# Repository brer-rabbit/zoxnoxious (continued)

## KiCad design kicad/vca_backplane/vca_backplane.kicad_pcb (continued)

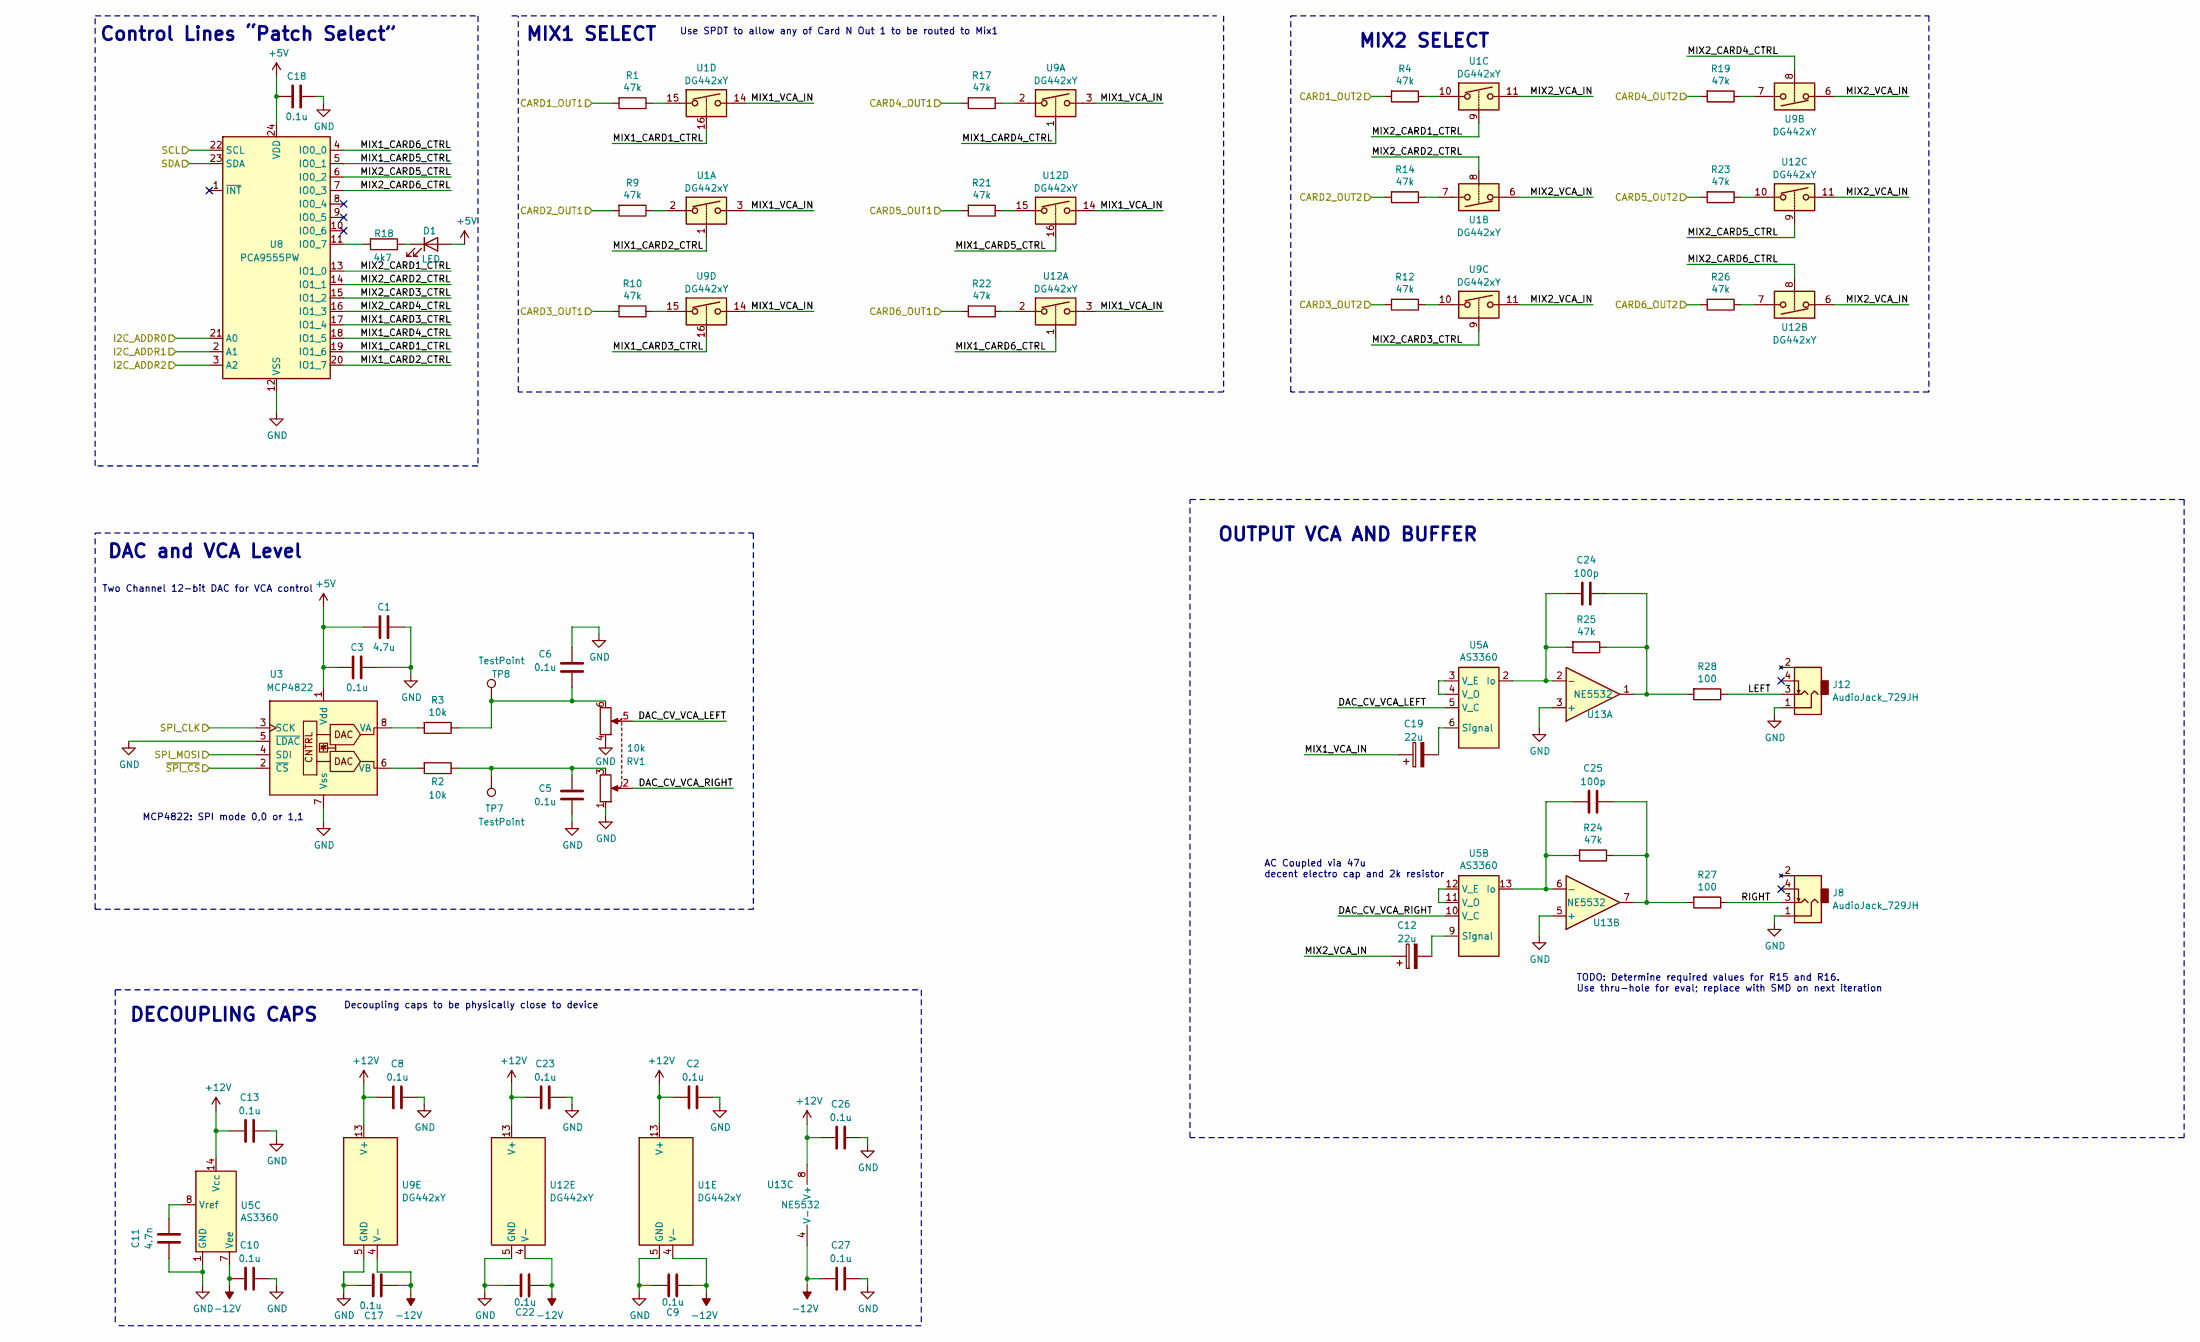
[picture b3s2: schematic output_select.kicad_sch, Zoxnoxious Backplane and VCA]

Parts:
C1: 4.7u; C_0805_2012Metric; LCSC C1779
C2, C3, C5, C6, C8, C9, C10, C13, C17, C18, C22, C23, C26, C27: 0.1u; C_0603_1608Metric; LCSC C14663
C11: 4.7n; C_0603_1608Metric; LCSC C53987
C12, C19: 22u; CP_Radial_D6.3mm_P2.50mm; Digikey 493-10780-1-ND
C24, C25: 100p; C_0603_1608Metric; LCSC C14858
D1: LED; LED_0603_1608Metric; LCSC C2286
J8, J12: AudioJack_729JH; Jack_3.5mm_729JH-R_Horizontal
R1, R4, R9, R10, R12, R14, R17, R19, R21, R22, R23, R24, R25, R26: 47k; R_0603_1608Metric; LCSC C25819
R2, R3: 10k; R_0603_1608Metric; LCSC C25804
R18: 4k7; R_0603_1608Metric; LCSC C23162
R27, R28: 100; R_0603_1608Metric; LCSC C22775
RV1: 10k; TRIM_PTN092-H10115K1B; Digikey PTN092-H10115K1A
TP7, TP8: TestPoint; TestPoint_Pad_2.0x2.0mm; Digikey 952-2664-2-ND
U1, U9, U12: DG442xY; SOIC-16_3.9x9.9mm_P1.27mm; LCSC C2673321
U3: MCP4822; SOIC-8_3.9x4.9mm_P1.27mm; LCSC C16040
U5: AS3360; SOIC-14_3.9x8.7mm_P1.27mm
U8: PCA9555PW; TSSOP-24_4.4x7.8mm_P0.65mm; LCSC C83265
U13: NE5532; SOIC-8_3.9x4.9mm_P1.27mm; LCSC C7426

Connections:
+5V: C1.2, C3.2, C18.2, D1.2 (A), U3.1 (Vdd), U8.2 (A1), U8.3 (A2), U8.21 (A0), U8.24 (VDD); also elsewhere on the board
+12V: C2.1, C8.1, C13.1, C23.1, C26.1, U1.13 (V+), U5.14 (Vcc), U9.13 (V+), U12.13 (V+), U13.8 (V+); also elsewhere on the board
-12V: C9.2, C10.1, C17.2, C22.2, C27.1, U1.4 (V-), U5.7 (Vee), U9.4 (V-), U12.4 (V-), U13.4 (V-); also elsewhere on the board
/CARD1_OUT1: R1.2; also elsewhere on the board
/CARD1_OUT2: R4.2; also elsewhere on the board
/CARD2_OUT1: R9.2; also elsewhere on the board
/CARD2_OUT2: R14.2; also elsewhere on the board
/CARD3_OUT1: R10.2; also elsewhere on the board
/CARD3_OUT2: R12.2; also elsewhere on the board
/CARD4_OUT1: R17.2; also elsewhere on the board
/CARD4_OUT2: R19.2; also elsewhere on the board
/CARD5_OUT1: R21.2; also elsewhere on the board
/CARD5_OUT2: R23.2; also elsewhere on the board
/CARD6_OUT1: R22.2; also elsewhere on the board
/CARD6_OUT2: R26.2; also elsewhere on the board
/SCL_5V: U8.22 (SCL); also elsewhere on the board
/SDA_5V: U8.23 (SDA); also elsewhere on the board
/SPI_CLK2_5V: U3.3 (SCK); also elsewhere on the board
/SPI_CS0_H: U3.2 (~CS); also elsewhere on the board
/SPI_MOSI2_5V: U3.4 (SDI); also elsewhere on the board
/Sheet624DD88D/DAC_CV_VCA_LEFT: RV1.5, U5.5 (V_C)
/Sheet624DD88D/DAC_CV_VCA_RIGHT: RV1.2, U5.10 (V_C)
/Sheet624DD88D/LEFT: J12.3, R28.1
/Sheet624DD88D/MIX1_CARD1_CTRL: U1.16, U8.19 (IO1_6)
/Sheet624DD88D/MIX1_CARD2_CTRL: U1.1, U8.20 (IO1_7)
/Sheet624DD88D/MIX1_CARD3_CTRL: U8.17 (IO1_4), U9.16
/Sheet624DD88D/MIX1_CARD4_CTRL: U8.18 (IO1_5), U9.1
/Sheet624DD88D/MIX1_CARD5_CTRL: U8.5 (IO0_1), U12.16
/Sheet624DD88D/MIX1_CARD6_CTRL: U8.4 (IO0_0), U12.1
/Sheet624DD88D/MIX1_VCA_IN: C19.1, U1.3, U1.14, U9.3, U9.14, U12.3, U12.14
/Sheet624DD88D/MIX2_CARD1_CTRL: U1.9, U8.13 (IO1_0)
/Sheet624DD88D/MIX2_CARD2_CTRL: U1.8, U8.14 (IO1_1)
/Sheet624DD88D/MIX2_CARD3_CTRL: U8.15 (IO1_2), U9.9
/Sheet624DD88D/MIX2_CARD4_CTRL: U8.16 (IO1_3), U9.8
/Sheet624DD88D/MIX2_CARD5_CTRL: U8.6 (IO0_2), U12.9
/Sheet624DD88D/MIX2_CARD6_CTRL: U8.7 (IO0_3), U12.8
/Sheet624DD88D/MIX2_VCA_IN: C12.1, U1.6, U1.11, U9.6, U9.11, U12.6, U12.11
/Sheet624DD88D/RIGHT: J8.3, R27.1
GND: C1.1, C2.2, C3.1, C5.1, C6.2, C8.2, C9.1, C10.2, C11.1, C13.2, C17.1, C18.1, C22.1, C23.2, C26.2, C27.2, J8.1, J12.1, RV1.1, RV1.4, U1.5 (GND), U3.5 (~LDAC), U3.7 (Vss), U5.1 (GND), U8.12 (VSS), U9.5 (GND), U12.5 (GND), U13.3 (+), U13.5 (+); also elsewhere on the board
unnamed: C5.2, R2.1, RV1.3, TP7.1
unnamed: C6.1, R3.1, RV1.6, TP8.1
unnamed: C24.2, R25.1, R28.2, U13.1
unnamed: C25.2, R24.1, R27.2, U13.7
unnamed: D1.1 (K), R18.1
unnamed: R1.1, U1.15
unnamed: R4.1, U1.10
unnamed: R9.1, U1.2
unnamed: R10.1, U9.15
unnamed: R12.1, U9.10
unnamed: R14.1, U1.7
unnamed: R17.1, U9.2
unnamed: R19.1, U9.7
unnamed: R21.1, U12.15
unnamed: R22.1, U12.2
unnamed: R23.1, U12.10
unnamed: R26.1, U12.7
unnamed: R3.2, U3.8 (VA)
unnamed: R2.2, U3.6 (VB)
unnamed: C19.2, U5.6 (Signal)
unnamed: U5.3 (V_E), U5.4 (V_O)
unnamed: C12.2, U5.9 (Signal)
unnamed: U5.11 (V_O), U5.12 (V_E)
unnamed: C11.2, U5.8 (Vref)
unnamed: R18.2, U8.11 (IO0_7)
unnamed: C24.1, R25.2, U5.2 (Io), U13.2 (-)
unnamed: C25.1, R24.2, U5.13 (Io), U13.6 (-)

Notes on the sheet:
Two Channel 12-bit DAC for VCA control
DECOUPLING CAPS
TODO: Determine required values for R15 and R16. Use thru-hole for eval; replace with SMD on next iteration
Decoupling caps to be physically close to device
DAC and VCA Level
Use SPDT to allow any of Card N Out 1 to be routed to Mix1
MIX2 SELECT
OUTPUT VCA AND BUFFER
AC Coupled via 47u decent electro cap and 2k resistor
MCP4822: SPI mode 0,0 or 1,1
MIX1 SELECT
Control Lines “Patch Select”

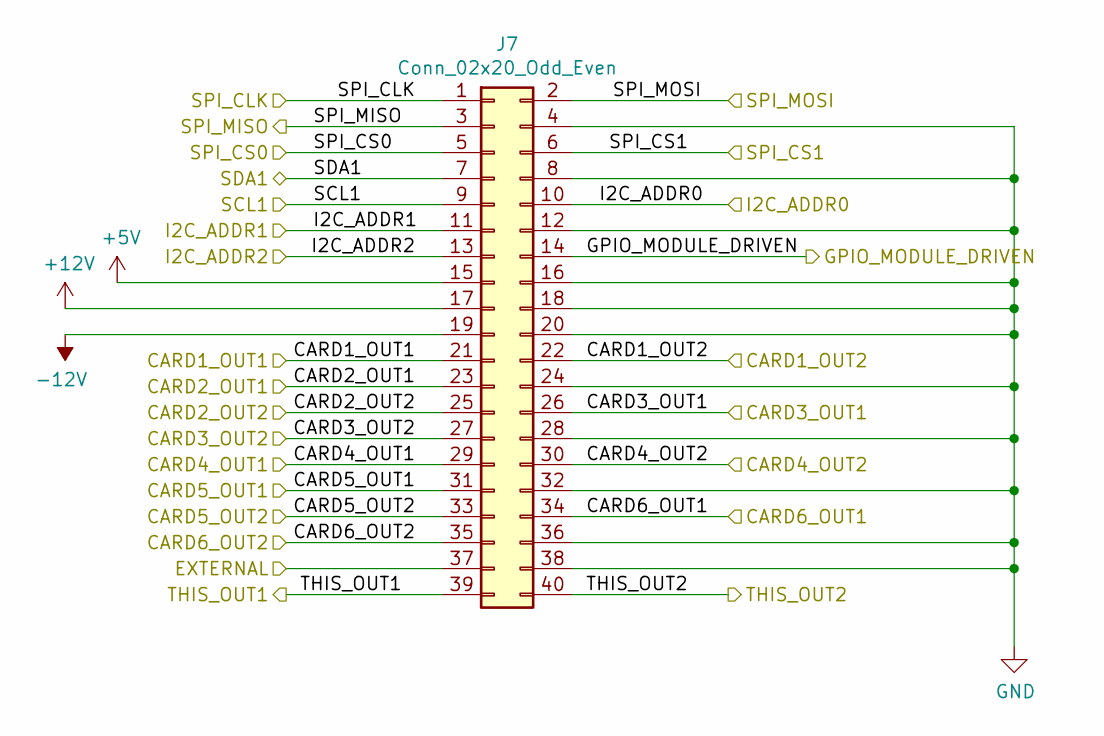
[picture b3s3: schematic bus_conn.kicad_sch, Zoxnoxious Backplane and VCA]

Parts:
J7: Conn_02x20_Odd_Even; PinSocket_2x20_P2.54mm_SullinsPolarized; Digikey S9200-ND

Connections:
+5V: J7.10, J7.11, J7.15; also elsewhere on the board
+12V: J7.17; also elsewhere on the board
-12V: J7.19; also elsewhere on the board
/CARD1_OUT1: J7.21; also elsewhere on the board
/CARD1_OUT2: J7.22; also elsewhere on the board
/CARD2_OUT1: J7.23; also elsewhere on the board
/CARD2_OUT2: J7.25; also elsewhere on the board
/CARD3_OUT1: J7.26; also elsewhere on the board
/CARD3_OUT2: J7.27; also elsewhere on the board
/CARD4_OUT1: J7.29, J7.39; also elsewhere on the board
/CARD4_OUT2: J7.30, J7.40; also elsewhere on the board
/CARD5_OUT1: J7.31; also elsewhere on the board
/CARD5_OUT2: J7.33; also elsewhere on the board
/CARD6_OUT1: J7.34; also elsewhere on the board
/CARD6_OUT2: J7.35; also elsewhere on the board
/EXTERNAL_AUDIO: J7.37; also elsewhere on the board
/MODULE_D_5V: J7.14; also elsewhere on the board
/SCL_5V: J7.9; also elsewhere on the board
/SDA_5V: J7.7; also elsewhere on the board
/SPI_CLK1_5V: J7.1; also elsewhere on the board
/SPI_CS0_D: J7.5; also elsewhere on the board
/SPI_CS1_D: J7.6; also elsewhere on the board
/SPI_MISO_5V: J7.3; also elsewhere on the board
/SPI_MOSI1_5V: J7.2; also elsewhere on the board
GND: J7.4, J7.8, J7.12, J7.13, J7.16, J7.18, J7.20, J7.24, J7.28, J7.32, J7.36, J7.38; also elsewhere on the board

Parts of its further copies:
J2, J3, J5, J10, J11: Conn_02x20_Odd_Even; PinSocket_2x20_P2.54mm_SullinsPolarized; Digikey S9200-ND

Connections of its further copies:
+5V: J2.10, J2.15, J3.15, J5.11, J5.15, J10.13, J10.15, J11.10, J11.13, J11.15; also elsewhere on the board
+12V: J2.17, J3.17, J5.17, J10.17, J11.17; also elsewhere on the board
-12V: J2.19, J3.19, J5.19, J10.19, J11.19; also elsewhere on the board
/CARD1_OUT1: J2.21, J3.21, J3.39, J5.21, J10.21, J11.21; also elsewhere on the board
/CARD1_OUT2: J2.22, J3.22, J3.40, J5.22, J10.22, J11.22; also elsewhere on the board
/CARD2_OUT1: J2.23, J2.39, J3.23, J5.23, J10.23, J11.23; also elsewhere on the board
/CARD2_OUT2: J2.25, J2.40, J3.25, J5.25, J10.25, J11.25; also elsewhere on the board
/CARD3_OUT1: J2.26, J3.26, J5.26, J5.39, J10.26, J11.26; also elsewhere on the board
/CARD3_OUT2: J2.27, J3.27, J5.27, J5.40, J10.27, J11.27; also elsewhere on the board
/CARD4_OUT1: J2.29, J3.29, J5.29, J10.29, J11.29; also elsewhere on the board
/CARD4_OUT2: J2.30, J3.30, J5.30, J10.30, J11.30; also elsewhere on the board
/CARD5_OUT1: J2.31, J3.31, J5.31, J10.31, J10.39, J11.31; also elsewhere on the board
/CARD5_OUT2: J2.33, J3.33, J5.33, J10.33, J10.40, J11.33; also elsewhere on the board
/CARD6_OUT1: J2.34, J3.34, J5.34, J10.34, J11.34, J11.39; also elsewhere on the board
/CARD6_OUT2: J2.35, J3.35, J5.35, J10.35, J11.35, J11.40; also elsewhere on the board
/EXTERNAL_AUDIO: J2.37, J3.37, J5.37, J10.37, J11.37; also elsewhere on the board
/MODULE_A_5V: J3.14; also elsewhere on the board
/MODULE_B_5V: J2.14; also elsewhere on the board
/MODULE_C_5V: J5.14; also elsewhere on the board
/MODULE_E_5V: J10.14; also elsewhere on the board
/MODULE_F_5V: J11.14; also elsewhere on the board
/SCL_5V: J2.9, J3.9, J5.9, J10.9, J11.9; also elsewhere on the board
/SDA_5V: J2.7, J3.7, J5.7, J10.7, J11.7; also elsewhere on the board
/SPI_CLK1_5V: J2.1, J5.1; also elsewhere on the board
/SPI_CLK2_5V: J3.1; also elsewhere on the board
/SPI_CLK3_5V: J10.1, J11.1; also elsewhere on the board
/SPI_CS0_A: J3.5; also elsewhere on the board
/SPI_CS0_B: J2.5; also elsewhere on the board
/SPI_CS0_C: J5.5; also elsewhere on the board
/SPI_CS0_E: J10.5; also elsewhere on the board
/SPI_CS0_F: J11.5; also elsewhere on the board
/SPI_CS1_A: J3.6; also elsewhere on the board
/SPI_CS1_B: J2.6; also elsewhere on the board
/SPI_CS1_C: J5.6; also elsewhere on the board
/SPI_CS1_E: J10.6; also elsewhere on the board
/SPI_CS1_F: J11.6; also elsewhere on the board
/SPI_MISO_5V: J2.3, J3.3, J5.3, J10.3, J11.3; also elsewhere on the board
/SPI_MOSI1_5V: J2.2, J5.2; also elsewhere on the board
/SPI_MOSI2_5V: J3.2; also elsewhere on the board
/SPI_MOSI3_5V: J10.2, J11.2; also elsewhere on the board
GND: J2.4, J2.8, J2.11, J2.12, J2.13, J2.16, J2.18, J2.20, J2.24, J2.28, J2.32, J2.36, J2.38, J3.4, J3.8, J3.10, J3.11, J3.12, J3.13, J3.16, J3.18, J3.20, J3.24, J3.28, J3.32, J3.36, J3.38, J5.4, J5.8, J5.10, J5.12, J5.13, J5.16, J5.18, J5.20, J5.24, J5.28, J5.32, J5.36, J5.38, J10.4, J10.8, J10.10, J10.11, J10.12, J10.16, J10.18, J10.20, J10.24, J10.28, J10.32, J10.36, J10.38, J11.4, J11.8, J11.11, J11.12, J11.16, J11.18, J11.20, J11.24, J11.28, J11.32, J11.36, J11.38; also elsewhere on the board

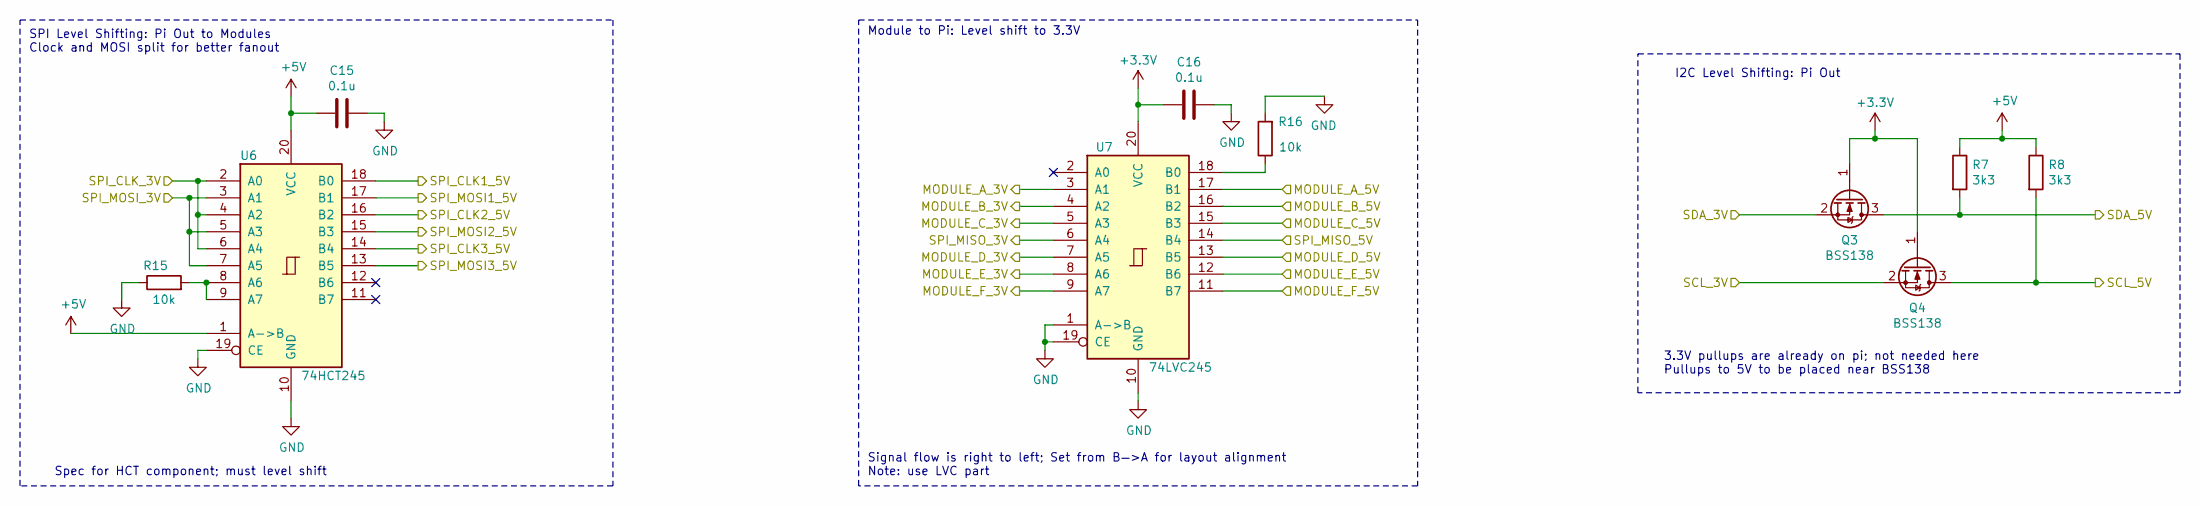
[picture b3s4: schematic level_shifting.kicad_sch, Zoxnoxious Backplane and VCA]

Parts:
C15, C16: 0.1u; C_0603_1608Metric; LCSC C14663
Q3, Q4: BSS138; SOT-23; LCSC C82045
R7, R8: 3k3; R_0603_1608Metric; LCSC C22978
R15, R16: 10k; R_0603_1608Metric; LCSC C25804
U6: 74HCT245; TSSOP-20_4.4x6.5mm_P0.65mm; LCSC C5980
U7: 74LVC245; TSSOP-20_4.4x6.5mm_P0.65mm; LCSC C6082

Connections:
+3.3V: C16.2, Q3.1 (G), Q4.1 (G), U7.20 (VCC); also elsewhere on the board
+5V: C15.2, R7.1, R8.1, U6.1 (A->B), U6.20 (VCC); also elsewhere on the board
/MODULE_A_3V: U7.3 (A1); also elsewhere on the board
/MODULE_A_5V: U7.17 (B1); also elsewhere on the board
/MODULE_B_3V: U7.4 (A2); also elsewhere on the board
/MODULE_B_5V: U7.16 (B2); also elsewhere on the board
/MODULE_C_3V: U7.5 (A3); also elsewhere on the board
/MODULE_C_5V: U7.15 (B3); also elsewhere on the board
/MODULE_D_3V: U7.7 (A5); also elsewhere on the board
/MODULE_D_5V: U7.13 (B5); also elsewhere on the board
/MODULE_E_3V: U7.8 (A6); also elsewhere on the board
/MODULE_E_5V: U7.12 (B6); also elsewhere on the board
/MODULE_F_3V: U7.9 (A7); also elsewhere on the board
/MODULE_F_5V: U7.11 (B7); also elsewhere on the board
/SCL1: Q4.2 (S); also elsewhere on the board
/SCL_5V: Q4.3 (D), R8.2; also elsewhere on the board
/SDA1: Q3.2 (S); also elsewhere on the board
/SDA_5V: Q3.3 (D), R7.2; also elsewhere on the board
/SPI_CLK: U6.2 (A0), U6.4 (A2), U6.6 (A4); also elsewhere on the board
/SPI_CLK1_5V: U6.18 (B0); also elsewhere on the board
/SPI_CLK2_5V: U6.16 (B2); also elsewhere on the board
/SPI_CLK3_5V: U6.14 (B4); also elsewhere on the board
/SPI_MISO: U7.6 (A4); also elsewhere on the board
/SPI_MISO_5V: U7.14 (B4); also elsewhere on the board
/SPI_MOSI: U6.3 (A1), U6.5 (A3), U6.7 (A5); also elsewhere on the board
/SPI_MOSI1_5V: U6.17 (B1); also elsewhere on the board
/SPI_MOSI2_5V: U6.15 (B3); also elsewhere on the board
/SPI_MOSI3_5V: U6.13 (B5); also elsewhere on the board
GND: C15.1, C16.1, R15.1, R16.2, U6.10 (GND), U6.19 (CE), U7.1 (A->B), U7.10 (GND), U7.19 (CE); also elsewhere on the board
unnamed: R15.2, U6.8 (A6), U6.9 (A7)
unnamed: R16.1, U7.18 (B0)

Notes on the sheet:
SPI Level Shifting: Pi Out to Modules Clock and MOSI split for better fanout
I2C Level Shifting: Pi Out
Module to Pi: Level shift to 3.3V
Spec for HCT component; must level shift
3.3V pullups are already on pi; not needed here Pullups to 5V to be placed near BSS138
Signal flow is right to left; Set from B—>A for layout alignment Note: use LVC part

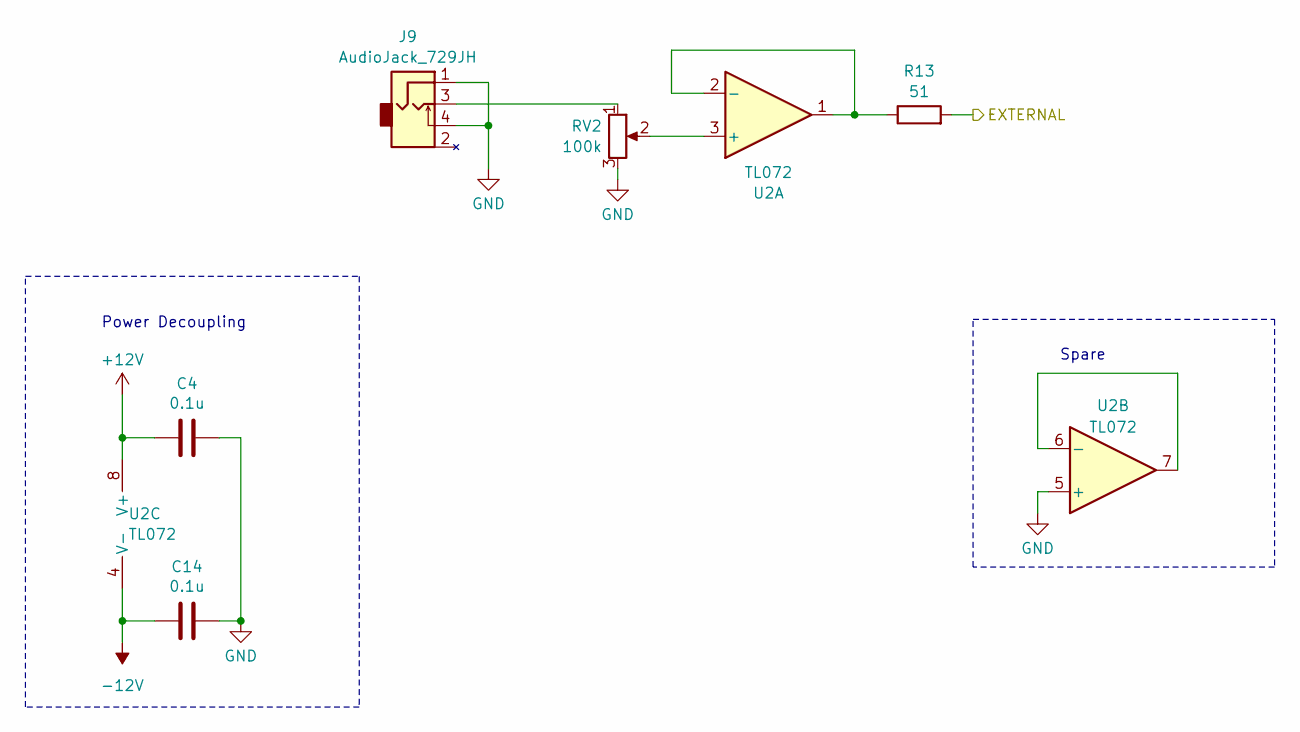
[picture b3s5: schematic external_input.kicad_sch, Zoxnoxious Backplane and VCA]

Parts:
C4, C14: 0.1u; C_0603_1608Metric; LCSC C14663
J9: AudioJack_729JH; Jack_3.5mm_729JH-R_Horizontal
R13: 51; R_0603_1608Metric; LCSC C23197
RV2: 100k; TRIM_PTN091-H10115K1B; Digikey PTN091-H100115K1A
U2: TL072; SOIC-8_3.9x4.9mm_P1.27mm; LCSC C6961

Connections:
+12V: C4.2, U2.8 (V+); also elsewhere on the board
-12V: C14.2, U2.4 (V-); also elsewhere on the board
/EXTERNAL_AUDIO: R13.2; also elsewhere on the board
GND: C4.1, C14.1, J9.1, J9.4, RV2.3, U2.5 (+); also elsewhere on the board
unnamed: J9.3, RV2.1
unnamed: RV2.2, U2.3 (+)
unnamed: R13.1, U2.1, U2.2 (-)
unnamed: U2.6 (-), U2.7

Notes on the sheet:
Spare
Power Decoupling

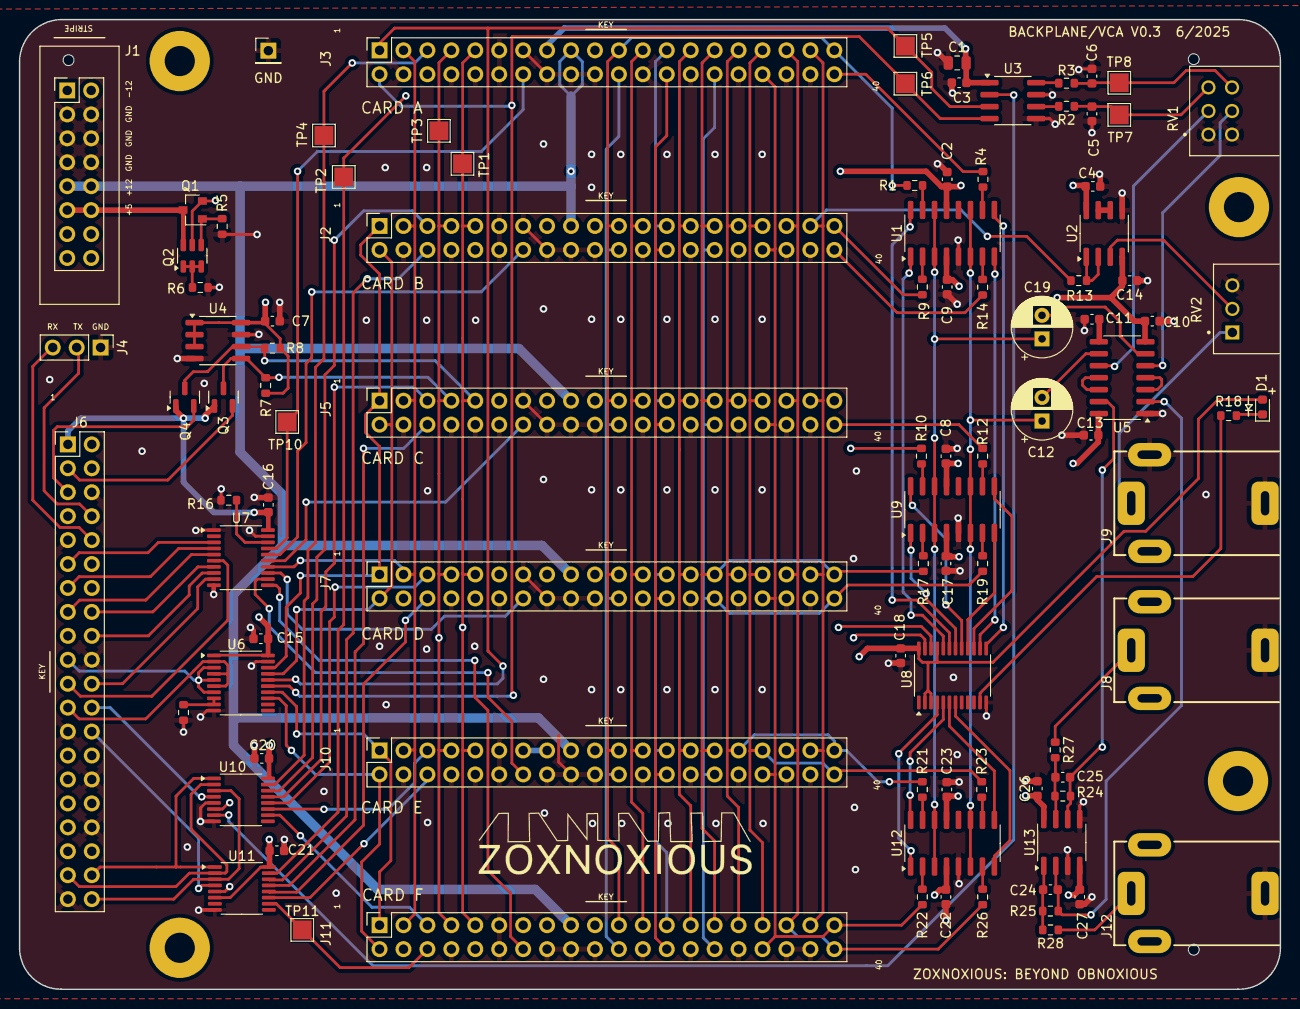
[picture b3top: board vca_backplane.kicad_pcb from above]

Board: 4 copper layers, 133.8 x 102.9 mm, 100 parts (0 on the bottom side), 118 nets.

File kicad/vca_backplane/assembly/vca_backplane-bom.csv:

Comment,Designator,Footprint,LCSC Part #
"4.7u","C1","Capacitor_SMD:C_0805_2012Metric","C1779"
"4.7n","C11","Capacitor_SMD:C_0603_1608Metric","C53987"
"100p","C24,C25","Capacitor_SMD:C_0603_1608Metric","C14858"
"0.1u","C2,C3,C4,C5,C6,C7,C8,C9,C10,C13,C14,C15,C16,C17,C18,C20,C21,C22,C23,C26,C27","Capacitor_SMD:C_0603_1608Metric","C14663"
"LED","D1","LED_SMD:LED_0603_1608Metric","C2286"
"DMG2305UX","Q1","project_footprints:SOT-23-DMG2305UX","C150470"
"DMMT5401","Q2","Package_TO_SOT_SMD:SOT-23-6","C154733"
"BSS138","Q3,Q4","Package_TO_SOT_SMD:SOT-23","C82045"
"51","R13","Resistor_SMD:R_0603_1608Metric","C23197"
"4k7","R18","Resistor_SMD:R_0603_1608Metric","C23162"
"100","R27,R28","Resistor_SMD:R_0603_1608Metric","C22775"
"47k","R1,R4,R5,R9,R10,R12,R14,R17,R19,R21,R22,R23,R24,R25,R26","Resistor_SMD:R_0603_1608Metric","C25819"
"10k","R2,R3,R6,R15,R16","Resistor_SMD:R_0603_1608Metric","C25804"
"3k3","R7,R8","Resistor_SMD:R_0603_1608Metric","C22978"
"DG442xY","U1,U9,U12","Package_SO:SOIC-16_3.9x9.9mm_P1.27mm","C2673321"
"74HCT138","U10,U11","Package_SO:TSSOP-16_4.4x5mm_P0.65mm","C8115"
"NE5532","U13","Package_SO:SOIC-8_3.9x4.9mm_P1.27mm","C7426"
"TL072","U2","Package_SO:SOIC-8_3.9x4.9mm_P1.27mm","C6961"
"MCP4822","U3","Package_SO:SOIC-8_3.9x4.9mm_P1.27mm","C16040"
"M24C02-WMN","U4","Package_SO:SOIC-8_3.9x4.9mm_P1.27mm","C7562"
"74HCT245","U6","Package_SO:TSSOP-20_4.4x6.5mm_P0.65mm","C5980"
"74LVC245","U7","Package_SO:TSSOP-20_4.4x6.5mm_P0.65mm","C6082"
"PCA9555PW","U8","Package_SO:TSSOP-24_4.4x7.8mm_P0.65mm","C83265"

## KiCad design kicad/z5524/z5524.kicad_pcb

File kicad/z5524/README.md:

# Z5524 Dual VCO Synth Voice

The Z5524 is a full dual VCO synth voice.  The first VCO is based around an SSI2130 and features thru zero frequency modulation (TZFM).  The second VCO is from the AS3394 synth-on-a-chip.  Both VCOs run through the AS3394's VCF and VCA.

Some unique options with this setup such as combining soft sync with hard subsync, modulating the AS3394's waveselect, and some interesting options for the TZFM modulator from the AS3394 VCO.

# Block Diagram

# Resources

Datasheet TBD

[KiCanvas](https://kicanvas.org/?github=https%3A%2F%2Fgithub.com%2Fbrer-rabbit%2Fzoxnoxious%2Ftree%2Fmain%2Fkicad%2Fz5524)

# Demo

YouTube Demo

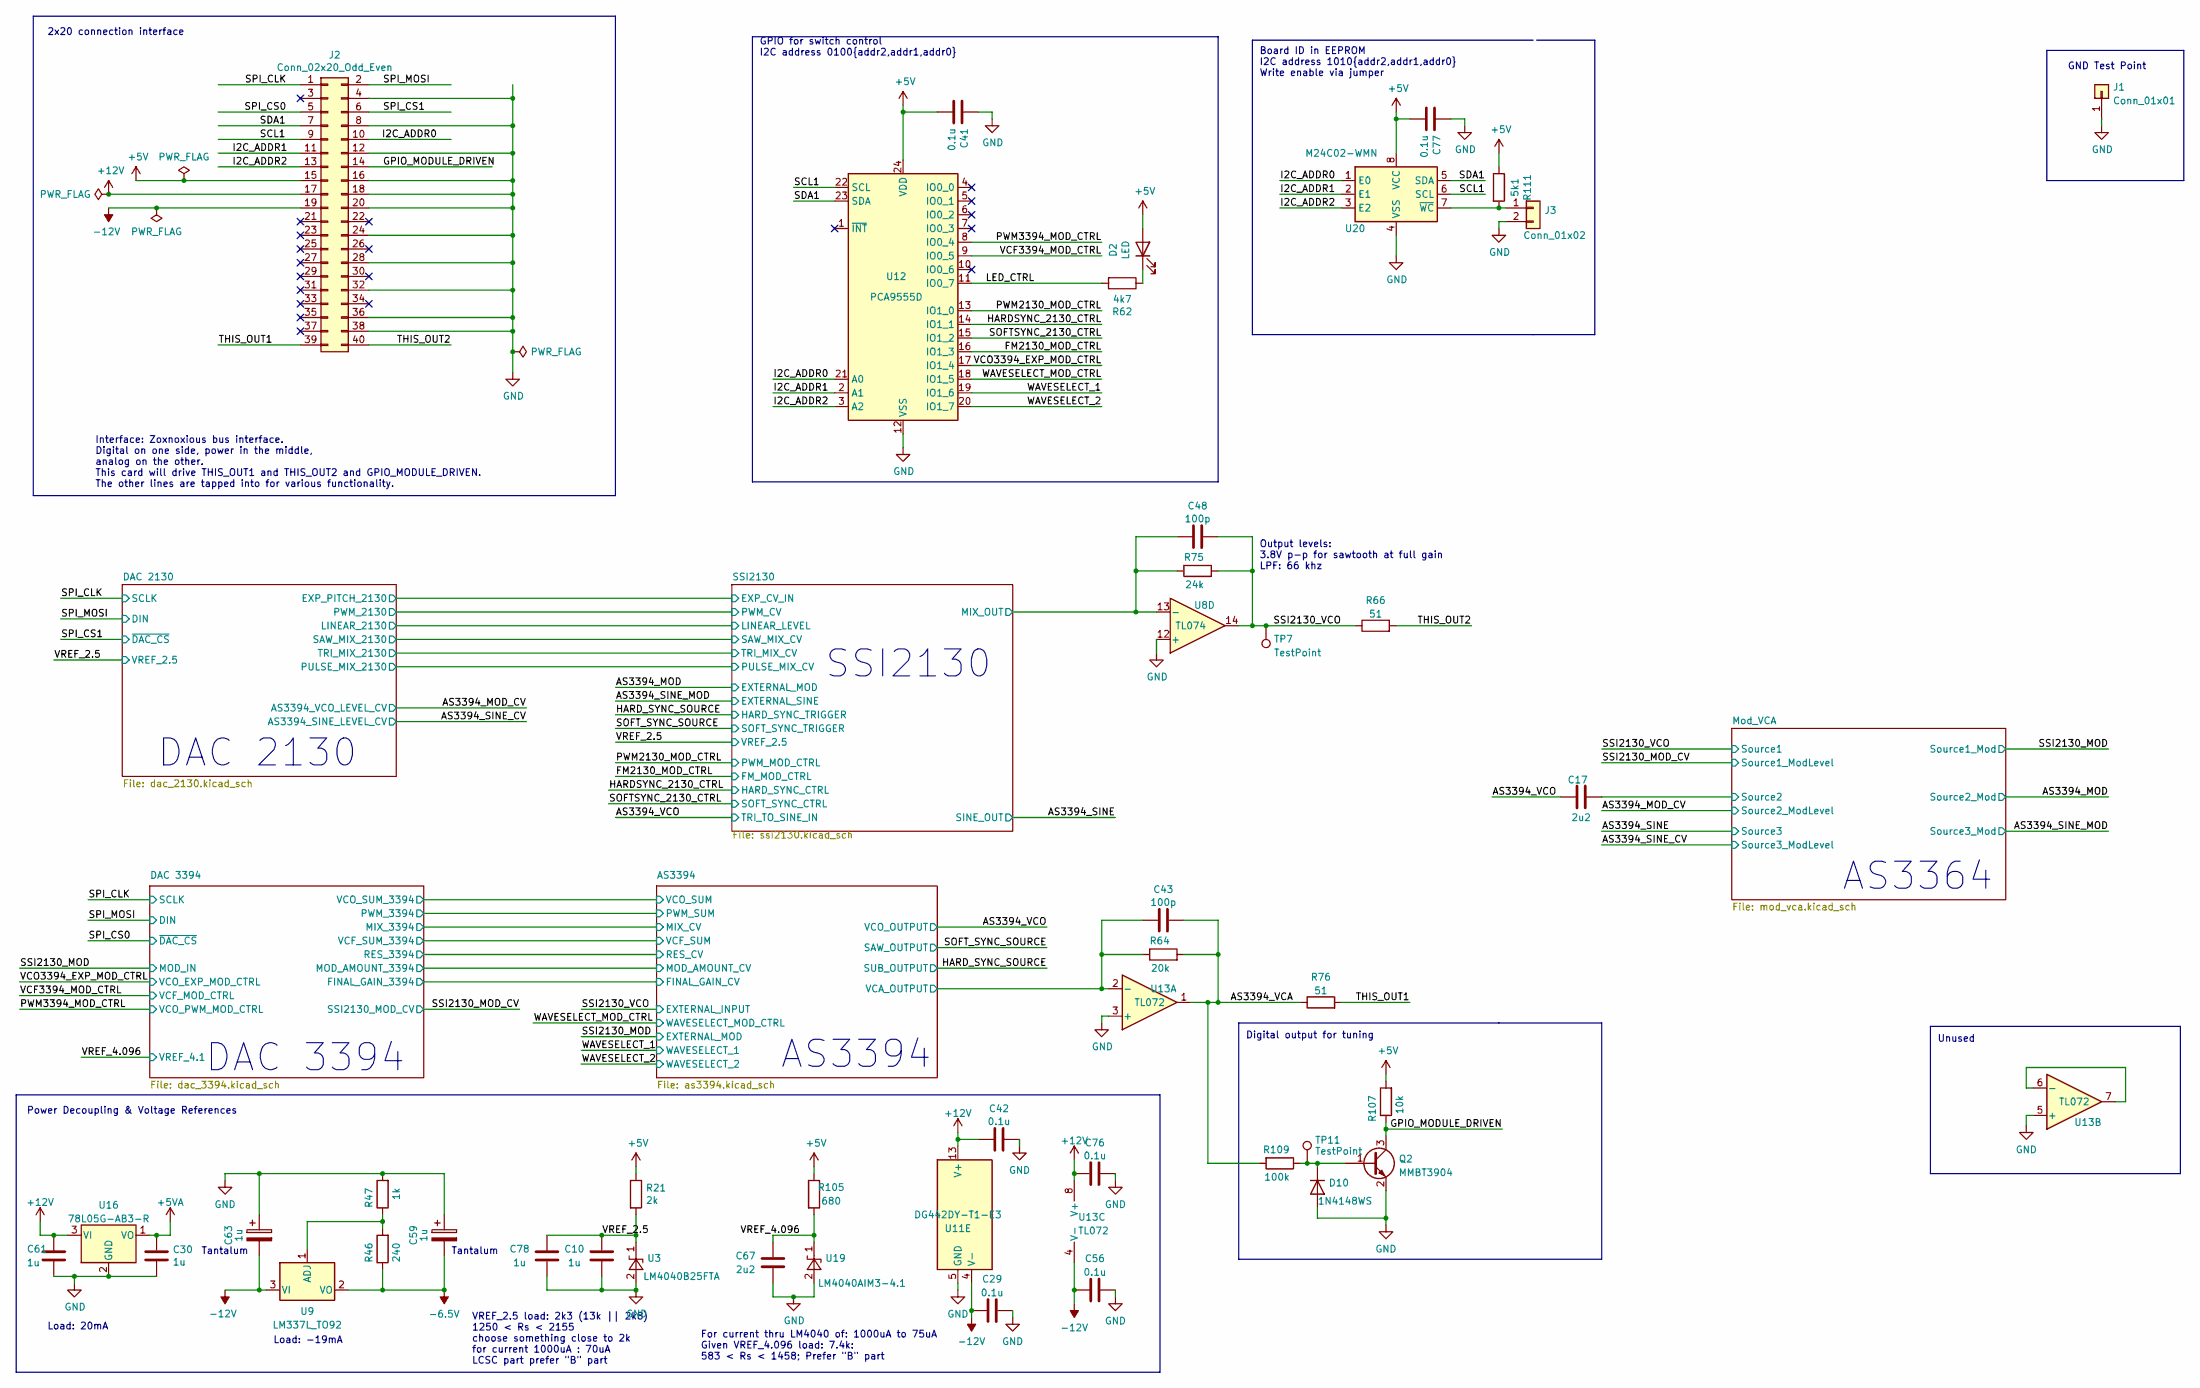
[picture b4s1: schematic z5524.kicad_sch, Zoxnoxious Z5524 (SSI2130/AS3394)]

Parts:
C10, C30, C61, C78: 1u; C_0603_1608Metric; LCSC C15849
C17, C67: 2u2; C_0603_1608Metric; LCSC C23630
C29, C41, C42, C56, C76, C77: 0.1u; C_0603_1608Metric; LCSC C14663
C43, C48: 100p; C_0603_1608Metric; LCSC C14858
C59, C63: 1u; CP_EIA-3216-10_Kemet-I; Mouser 80-T491A105K016
D2: LED; LED_0603_1608Metric; LCSC C2286
D10: 1N4148WS; D_SOD-323; LCSC C2128
J1: Conn_01x01; PinHeader_1x01_P2.54mm_Vertical
J2: Conn_02x20_Odd_Even; PinHeader_2x20_P2.54mm_Horizontal
J3: Conn_01x02; PinHeader_1x02_P2.54mm_Vertical
Q2: MMBT3904; SOT-23; LCSC C20526
R21: 2k; R_0603_1608Metric; LCSC C22975
R46: 240; R_0805_2012Metric; LCSC C17572
R47: 1k; R_0603_1608Metric; LCSC C21190
R62: 4k7; R_0603_1608Metric; LCSC C23162
R64: 20k; R_0603_1608Metric; LCSC C4184
R66, R76: 51; R_0603_1608Metric; LCSC C23197
R75: 24k; R_0603_1608Metric; LCSC C23352
R105: 680; R_0603_1608Metric; LCSC C23228
R107: 10k; R_0603_1608Metric; LCSC C25804
R109: 100k; R_0603_1608Metric; LCSC C25803
R111: 5k1; R_0603_1608Metric; LCSC C23186
TP7, TP11: TestPoint; TestPoint_Pad_1.5x1.5mm
U3: LM4040B25FTA; SOT-23; LCSC C460725
U8: TL074; TSSOP-14_4.4x5mm_P0.65mm; LCSC C96507
U9: LM337L_TO92; TO-92_Inline_Wide
U11: DG442DY-T1-E3; SOIC-16_3.9x9.9mm_P1.27mm; LCSC C2673321
U12: PCA9555D; TSSOP-24_4.4x7.8mm_P0.65mm; LCSC C83265
U13: TL072; SO-8_3.9x4.9mm_P1.27mm; LCSC C6961
U16: 78L05G-AB3-R; SOT-89-3; LCSC C71136
U19: LM4040AIM3-4.1; SOT-23; LCSC C126807
U20: M24C02-WMN; SOIC-8_3.9x4.9mm_P1.27mm; LCSC C7562

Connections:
+5V: C41.2, C77.2, D2.2 (A), J2.15, R21.1, R105.1, R107.2, R111.1, U12.24 (VDD), U20.8 (VCC); also elsewhere on the board
+5VA: C30.1, U16.1 (VO); also elsewhere on the board
+12V: C42.1, C61.1, C76.1, J2.17, U11.13 (V+), U13.8 (V+), U16.3 (VI); also elsewhere on the board
-6V: C59.2, R46.1, U9.2 (VO); also elsewhere on the board
-12V: C29.1, C56.1, C63.2, J2.19, U9.3 (VI), U11.4 (V-), U13.4 (V-); also elsewhere on the board
/AS3394/VCA_OUTPUT: C43.1, R64.1, U13.2 (-); also elsewhere on the board
/AS3394_VCA: C43.2, R64.2, R76.1, R109.2, U13.1
/AS3394_VCO: C17.2; also elsewhere on the board
/FM2130_MOD_CTRL: U12.16 (IO1_3); also elsewhere on the board
/GPIO_MODULE_DRIVEN: J2.14, Q2.3 (C), R107.1
/HARDSYNC_2130_CTRL: U12.14 (IO1_1); also elsewhere on the board
/I2C_ADDR0: J2.10, U12.21 (A0), U20.1 (E0)
/I2C_ADDR1: J2.11, U12.2 (A1), U20.2 (E1)
/I2C_ADDR2: J2.13, U12.3 (A2), U20.3 (E2)
/LED_CTRL: R62.2, U12.11 (IO0_7)
/Mod_VCA/Source2: C17.1; also elsewhere on the board
/PWM2130_MOD_CTRL: U12.13 (IO1_0); also elsewhere on the board
/PWM3394_MOD_CTRL: U12.8 (IO0_4); also elsewhere on the board
/SCL1: J2.9, U12.22 (SCL), U20.6 (SCL)
/SDA1: J2.7, U12.23 (SDA), U20.5 (SDA)
/SOFTSYNC_2130_CTRL: U12.15 (IO1_2); also elsewhere on the board
/SPI_CLK: J2.1; also elsewhere on the board
/SPI_CS0: J2.5; also elsewhere on the board
/SPI_CS1: J2.6; also elsewhere on the board
/SPI_MOSI: J2.2; also elsewhere on the board
/SSI2130/MIX_OUT: C48.1, R75.1, U8.13 (-); also elsewhere on the board
/SSI2130_VCO: C48.2, R66.1, R75.2, TP7.1, U8.14; also elsewhere on the board
/THIS_OUT1: J2.39, R76.2
/THIS_OUT2: J2.40, R66.2
/VCF3394_MOD_CTRL: U12.9 (IO0_5); also elsewhere on the board
/VCO3394_EXP_MOD_CTRL: U12.17 (IO1_4); also elsewhere on the board
/VREF_2.5: C10.1, C78.1, R21.2, U3.1 (K); also elsewhere on the board
/VREF_4.096: C67.2, R105.2, U19.1 (K); also elsewhere on the board
/WAVESELECT_1: U12.19 (IO1_6); also elsewhere on the board
/WAVESELECT_2: U12.20 (IO1_7); also elsewhere on the board
/WAVESELECT_MOD_CTRL: U12.18 (IO1_5); also elsewhere on the board
GND: C10.2, C29.2, C30.2, C41.1, C42.2, C56.2, C59.1, C61.2, C63.1, C67.1, C76.2, C77.1, C78.2, D10.2 (A), J1.1, J2.4, J2.8, J2.12, J2.16, J2.18, J2.20, J2.24, J2.28, J2.32, J2.36, J2.38, J3.2, Q2.2 (E), R47.2, U3.2 (A), U8.12 (+), U11.5 (GND), U12.12 (VSS), U13.3 (+), U13.5 (+), U16.2 (GND), U19.2 (A), U20.4 (VSS); also elsewhere on the board
unnamed: D2.1 (K), R62.1
unnamed: D10.1 (K), Q2.1 (B), R109.1, TP11.1
unnamed: J3.1, R111.2, U20.7 (~WC)
unnamed: R46.2, R47.1, U9.1 (ADJ)
unnamed: U13.6 (-), U13.7

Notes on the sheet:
Power Decoupling & Voltage References
For current thru LM4040 of: 1000uA to 75uA Given VREF_4.096 load: 7.4k: 583 < Rs < 1458; Prefer "B" part
DAC 3394
Tantalum
Digital output for tuning
2x20 connection interface
Load: -19mA
SSI2130
VREF_2.5 load: 2k3 (13k || 2k8) 1250 < Rs < 2155 choose something close to 2k for current 1000uA : 70uA LCSC part prefer "B" part
GPIO for switch control I2C address 0100{addr2,addr1,addr0}
AS3364
Unused
AS3394
GND Test Point
Board ID in EEPROM I2C address 1010{addr2,addr1,addr0} Write enable via jumper
Interface: Zoxnoxious bus interface. Digital on one side, power in the middle, analog on the other. This card will drive THIS_OUT1 and THIS_OUT2 and GPIO_MODULE_DRIVEN. The other lines are tapped into for various functionality.
Output levels: 3.8V p-p for sawtooth at full gain LPF: 66 khz
DAC 2130
Load: 20mA
